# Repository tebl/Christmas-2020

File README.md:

# Christmas 2020
I wanted to do this project last year, but my health deteriorated and so the big Christmas 2019 project became the big Christmas 2020 project instead. 2020, if anything, provided plenty of time for sitting around the house thinking up how to make a blinking LED christmas tree with an Arduino Nano built into it! I even got around to adding a small video of it in action on [YouTube](https://www.youtube.com/watch?v=C256A0oTeUM)!

The project is composed of three PCB designs, parts A/B are the actual tree and have been made so that they slot into eachother. Part C is the base, it holds the Arduino Nano and a couple of shift registers in addition to a switch that is used in order to toggle the various modes (I added a second Part C board to the bottom to add a little more weight).

As with any Christmas tree, you can decorate it with any LEDs though you might need to adjust the resistor values accordingly so that some of them aren't extremely bright (when in doubt, try them on a breadboard first). Alternatively - you could choose to skip the whole decorating step and put some string at the top and hang it from your tree (you will need to use some wire on the bottom to keep it from falling apart).

## Building it
Start by examining all three PCBs, assuming you already have those handy - refer to the BOM below if you're wondering what parts to order from your favourite electronics boutique. Both of the A/B, the two tree parts should have a christmas bauble (at least I think that is the correct English translation of the round glass decorations) specifying both the part name (A or B) and wether you're looking at the front or the back. The latter details, the front and back bit, matters because this is the orientation it needs to be in when you want to slot it into the base (part C).

Because I wanted something that looked good without any components, parts A/B will look different from the standard markings used for LEDs and resistors you would expect to encounter any other time of the year. The baubles with the two holes are for LEDs, you can solder them straight on or aim them upwards if you'd like to - feel free to use those weird LEDs you got as a gift (it's your tree after all) - the important bit is that the **square pad** is for the negative leg of the LED (the **shorter** one). The squiggly lines are for the resistors, you need to pick values that work with your LEDs, so test them in a breadboard first in order to figure out which value to use (or just put 100 Ohm for the dim ones, 330 for the normal LEDs and something like 1K for those bright ones like the blue). Try installing components so that every side gets something, at least that's what my parents always instruct me to do on the big plastic tree.

Parts A/B are attached to the base using right-angle pin headers, take care that you match the orientation to the corresponding parts on part C. While on the subject of part C, the only important part here is that you'll probably need to solder the switch into place before putting in the Arduino Nano (unless you'll be using female header pins so that you can remove it later). The rest of the components (including the Nano) will be installed on the underside of part C.

Given that there are components on the underside of the base, you'll need to add some M3 hex spacers to it so that it won't scrape against the table - if you have an extra part C PCB I recommend putting it on the bottom as well so that it doesn't get knocked around so easily.

## BOM
The BOM, or bill of manufacturing, is a list of the components used when constructing the complete christmas tree. Note that since you can substitute the LEDs/resistors you want to use - the following may be more of a suggestion though you'd need all of it in order to make everything blink. Most of these components should be easily obtainable through your favourite local electronics components store. Right-angle pin headers are usually sold in breakable strips with 40 pins, so just break off 5 pin segments where needed.

| Reference    | Item                                       | Count |
| ------------ | ------------------------------------------ | ----- |
| Christmas A  | Fabricate using Gerber files ([order](https://www.pcbway.com/project/shareproject/Christmas_2020__part_A_.html))   |     1 |
| D1-D9        | LED (3mm or 5mm, colour as wanted)         |     9 |
| R1-R9        | 220, 330 or 1k ohm resistor *              |     9 |
| J1,J2        | 1x5-pin right-angle header                 |     2 |
| Christmas B  | Fabricate using Gerber files ([order](https://www.pcbway.com/project/shareproject/Christmas_2020__part_B_.html))   |     1 |
| D2-D9        | LED (3mm or 5mm, colour as wanted)         |     8 |
| R2-R9        | 220, 330 or 1k ohm resistor *              |     8 |
| J1,J2        | 1x5-pin right-angle header                 |     2 |
| Christmas C  | Fabricate using Gerber files ([order](https://www.pcbway.com/project/shareproject/Christmas_2020__part_C_.html))   |     1 |
| SW1          | SPST momentary push button                 |     1 |
| A1           | Arduino Nano                               |     1 |
| U1,U2        | 74HC595 (DIP-16)                           |     2 |
|              | M3 nylon hex standoffs with screws         |     4 |

*) Use resistors with values that would correspond to the LED you installed, use higher resistrance the brighter the LED (especially the blue ones). If a soldered in LED is too dim, install a lower value on the back as well in order to lower the resistance going to it.

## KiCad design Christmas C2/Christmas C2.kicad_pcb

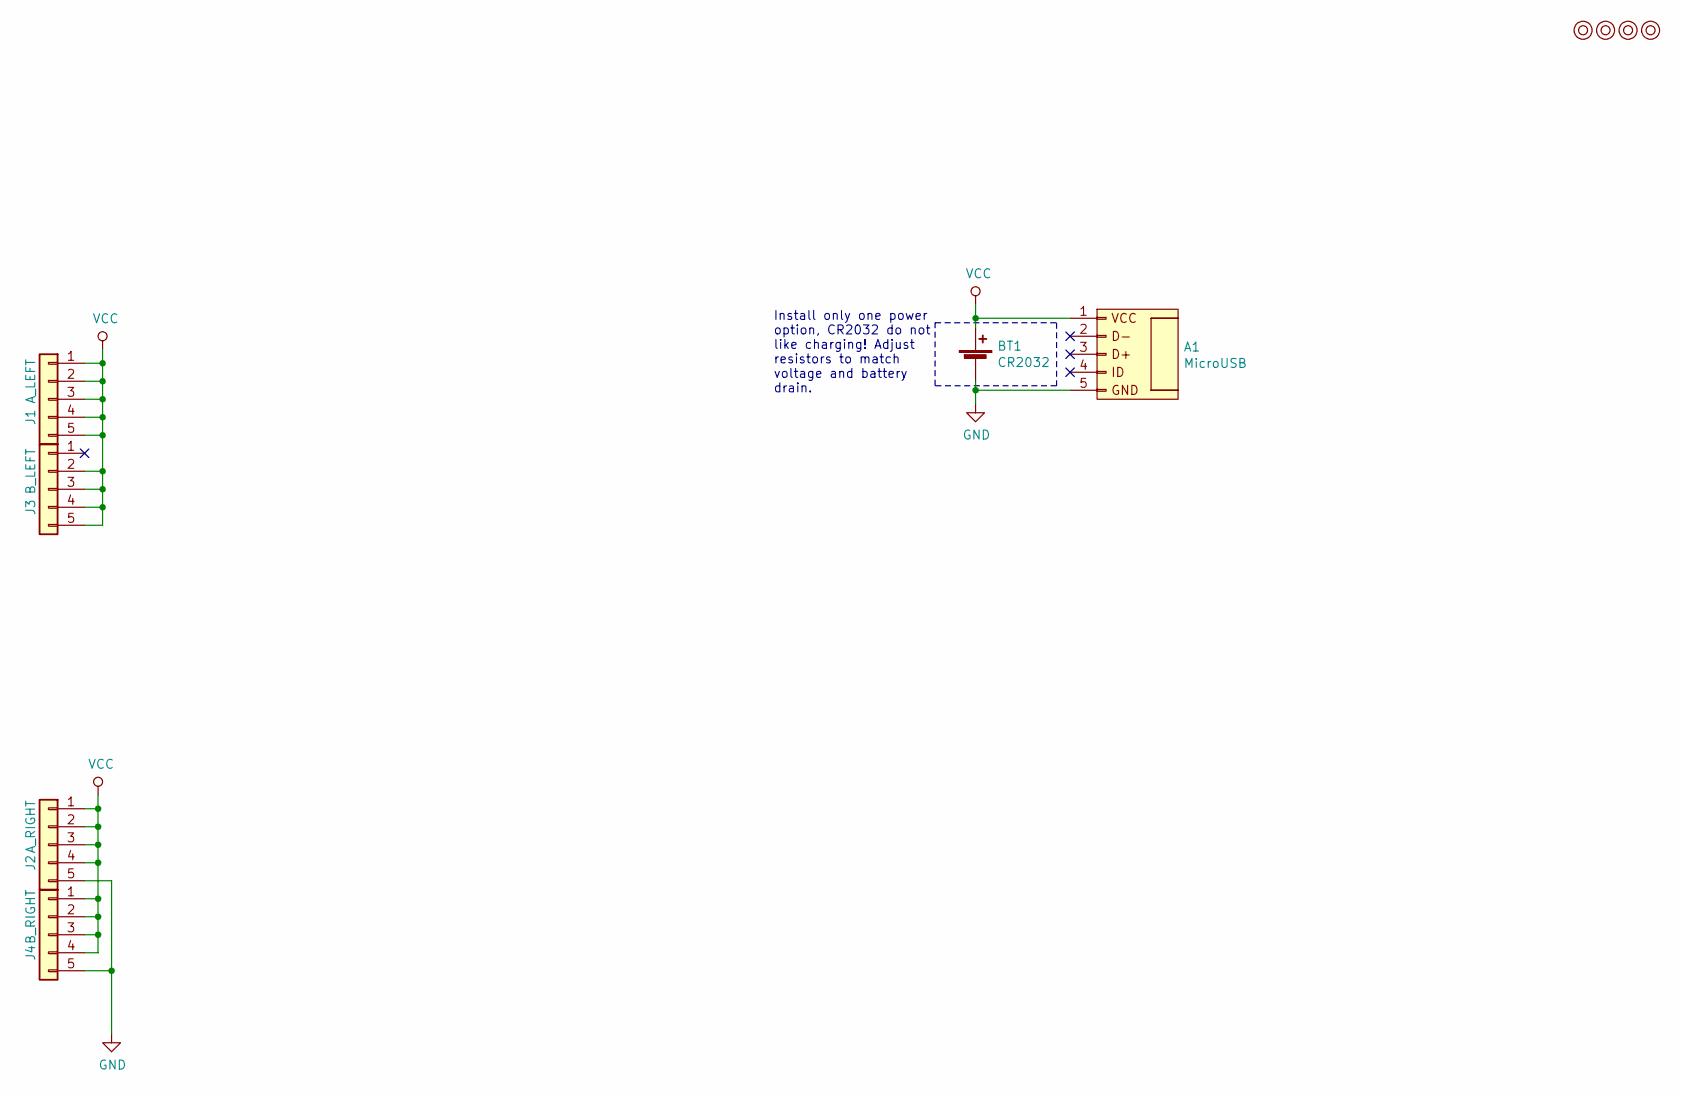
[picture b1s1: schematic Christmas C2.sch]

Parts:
A1: MicroUSB; microusb_breakout
BT1: CR2032; Keystone_103_1x20mm-CoinCell
J1: A_LEFT; conn_base
J2: A_RIGHT; conn_base
J3: B_LEFT; conn_base
J4: B_RIGHT; conn_base
M1, M2, M3, M4: Mounting; M3

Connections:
GND: A1.5 (GND), BT1.2 (-), J2.5, J4.5
VCC: A1.1 (VCC), BT1.1 (+), J1.1, J1.2, J1.3, J1.4, J1.5, J2.1, J2.2, J2.3, J2.4, J3.2, J3.3, J3.4, J3.5, J4.1, J4.2, J4.3, J4.4

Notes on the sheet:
Install only one power option, CR2032 do not like charging! Adjust resistors to match voltage and battery drain.

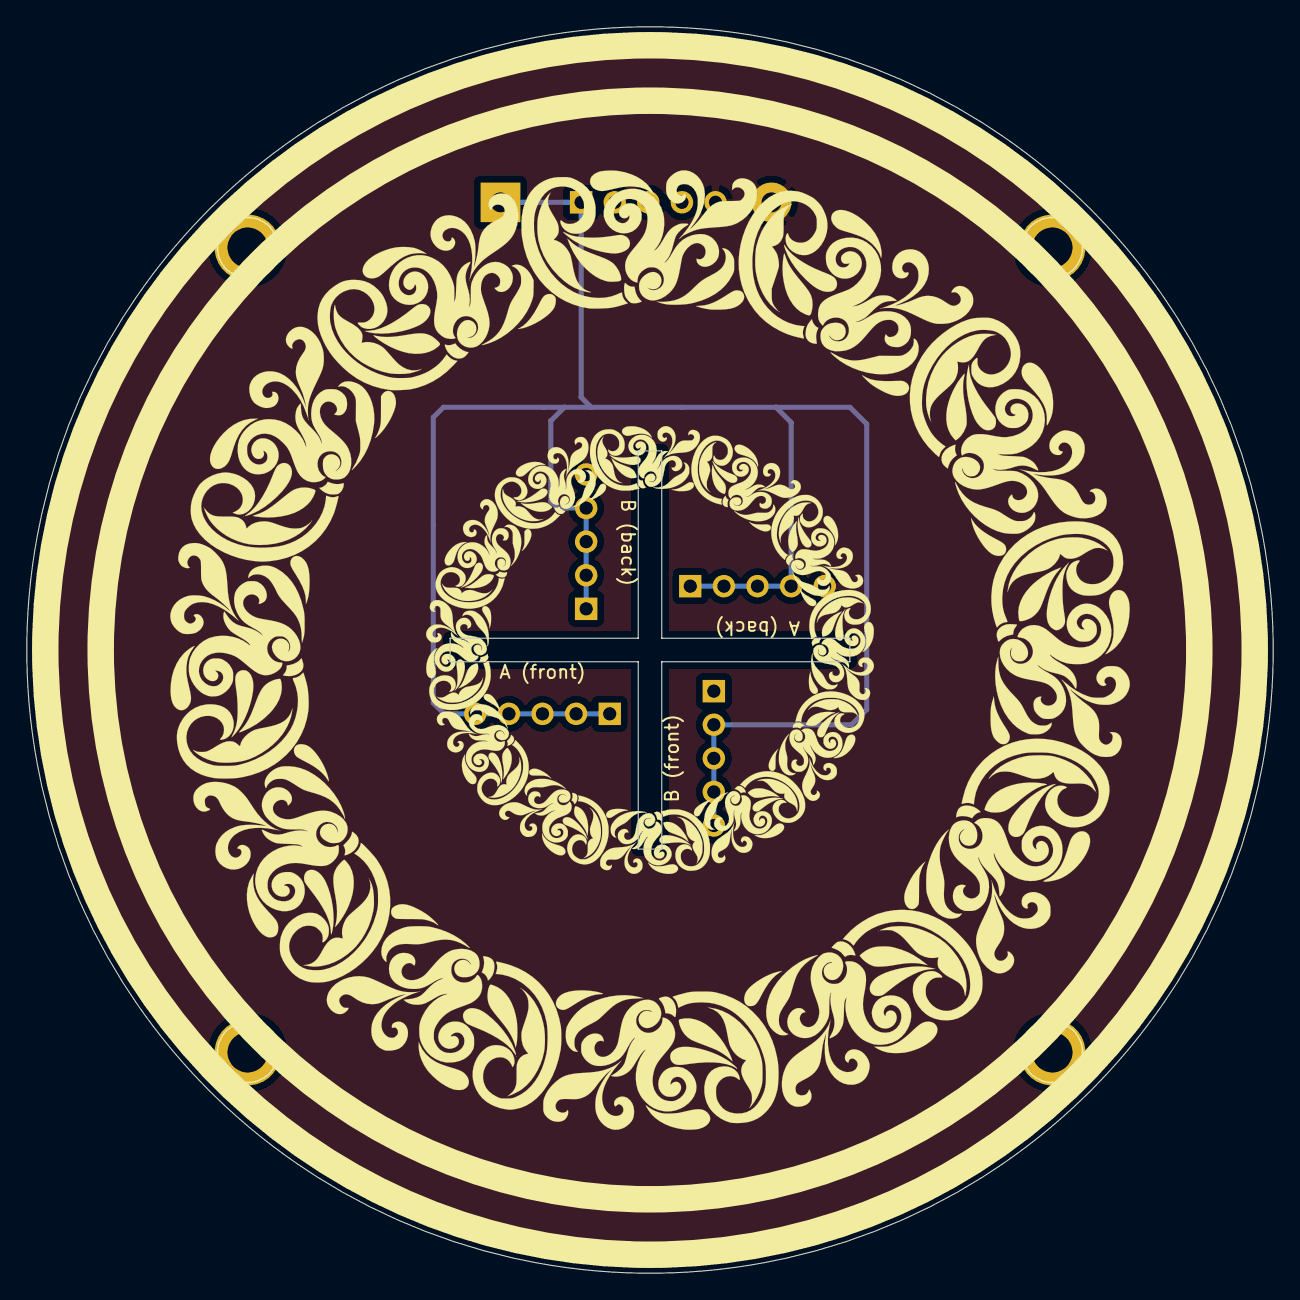
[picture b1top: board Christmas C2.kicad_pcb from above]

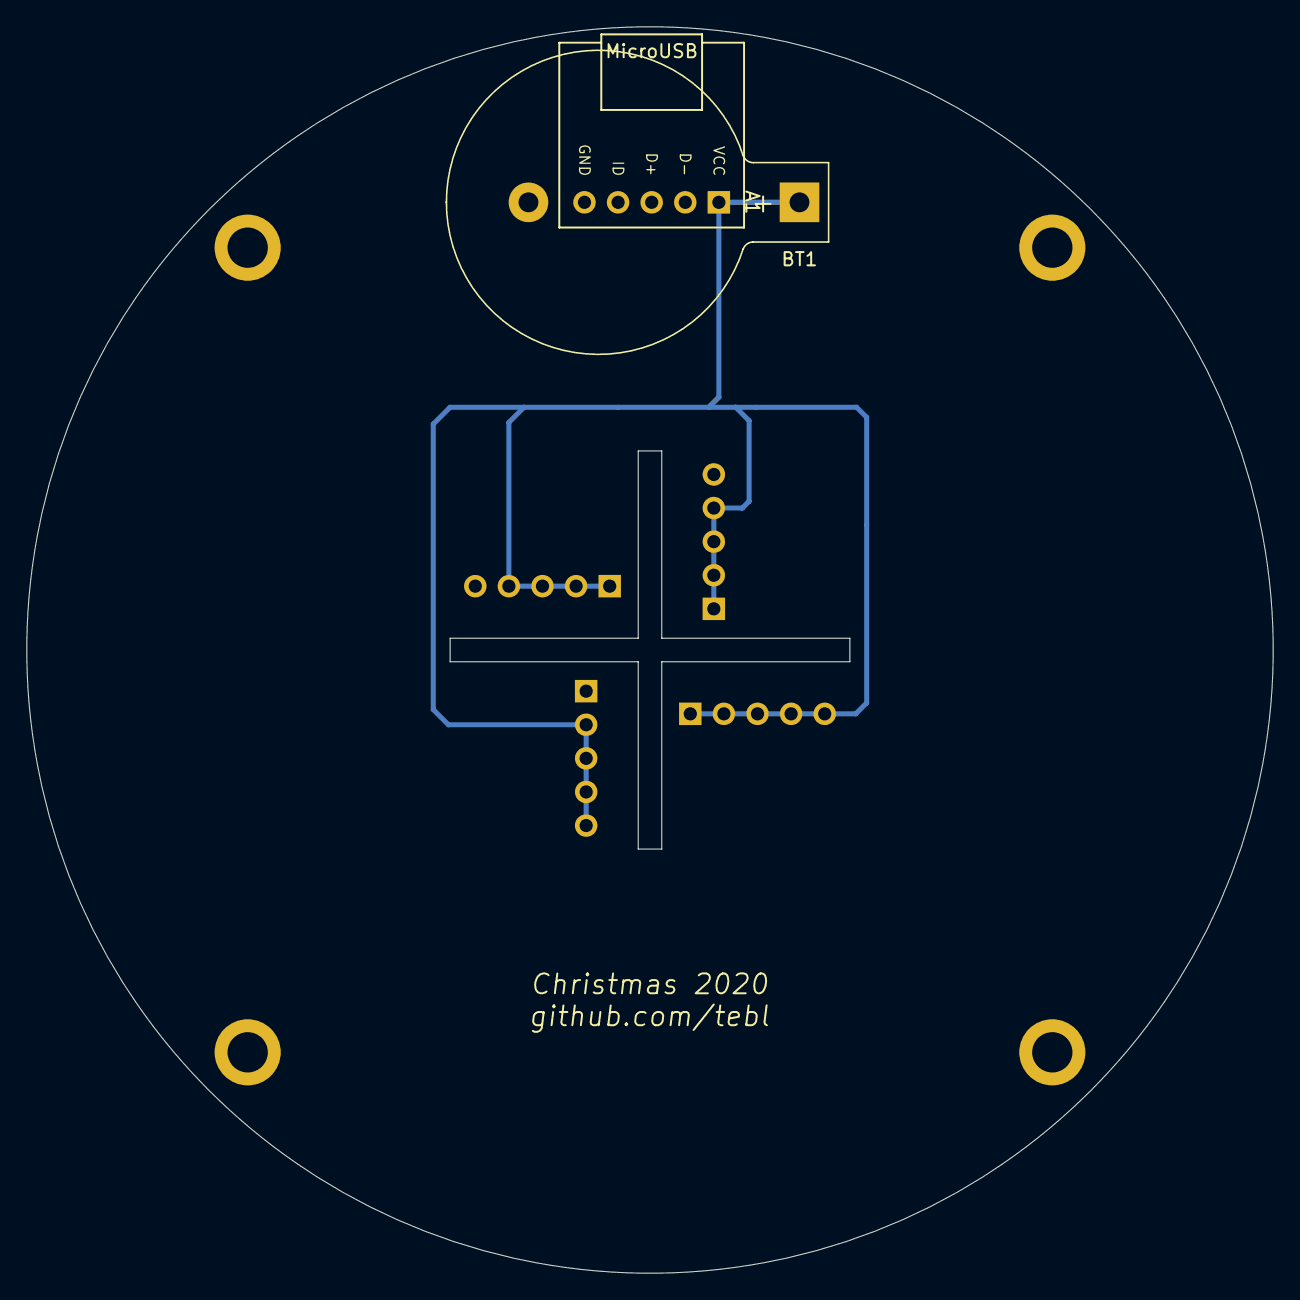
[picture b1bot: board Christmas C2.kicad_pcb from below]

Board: 2 copper layers, 94.2 x 94.2 mm, 10 parts (2 on the bottom side), 2 nets.

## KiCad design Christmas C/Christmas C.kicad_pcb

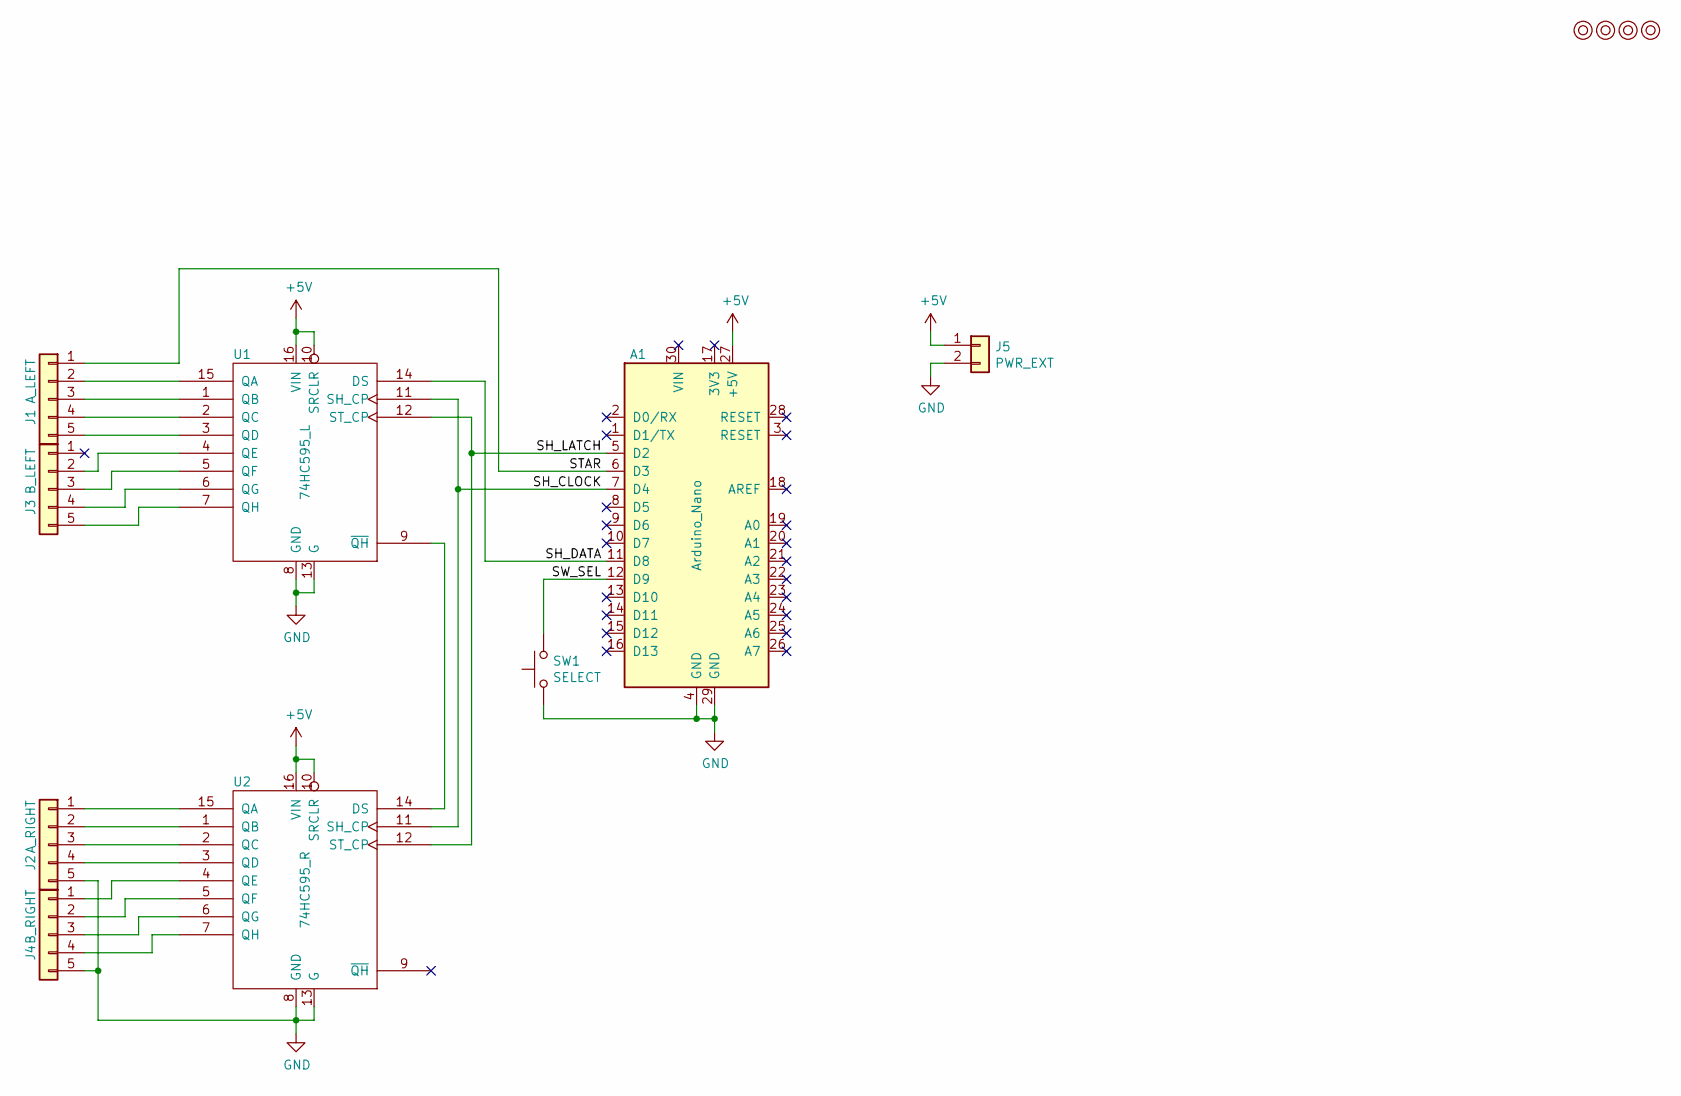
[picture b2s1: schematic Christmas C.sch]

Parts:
A1: Arduino_Nano
J1: A_LEFT; conn_base
J2: A_RIGHT; conn_base
J3: B_LEFT; conn_base
J4: B_RIGHT; conn_base
J5: PWR_EXT; Pin_Header_Straight_1x02_Pitch2.54mm
M1, M2, M3, M4: Mounting; M3
SW1: SELECT; SW_PUSH_6mm
U1: 74HC595_L; DIP-16_W7.62mm_LongPads
U2: 74HC595_R; DIP-16_W7.62mm_LongPads

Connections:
+5V: A1.27 (+5V), J5.1, U1.10 (SRCLR), U1.16 (VIN), U2.10 (SRCLR), U2.16 (VIN)
/SH_CLOCK: A1.7 (D4), U1.11 (SH_CP), U2.11 (SH_CP)
/SH_DATA: A1.11 (D8), U1.14 (DS)
/SH_LATCH: A1.5 (D2), U1.12 (ST_CP), U2.12 (ST_CP)
/STAR: A1.6 (D3), J1.1
/SW_SEL: A1.12 (D9), SW1.2
GND: A1.4 (GND), A1.29 (GND), J2.5, J4.5, J5.2, SW1.1, U1.8 (GND), U1.13 (G), U2.8 (GND), U2.13 (G)
unnamed: J1.2, U1.15 (QA)
unnamed: J1.3, U1.1 (QB)
unnamed: J1.4, U1.2 (QC)
unnamed: J1.5, U1.3 (QD)
unnamed: J2.1, U2.15 (QA)
unnamed: J2.2, U2.1 (QB)
unnamed: J2.3, U2.2 (QC)
unnamed: J2.4, U2.3 (QD)
unnamed: J3.2, U1.4 (QE)
unnamed: J3.3, U1.5 (QF)
unnamed: J3.4, U1.6 (QG)
unnamed: J3.5, U1.7 (QH)
unnamed: J4.1, U2.4 (QE)
unnamed: J4.2, U2.5 (QF)
unnamed: J4.3, U2.6 (QG)
unnamed: J4.4, U2.7 (QH)
unnamed: U1.9 (~QH), U2.14 (DS)

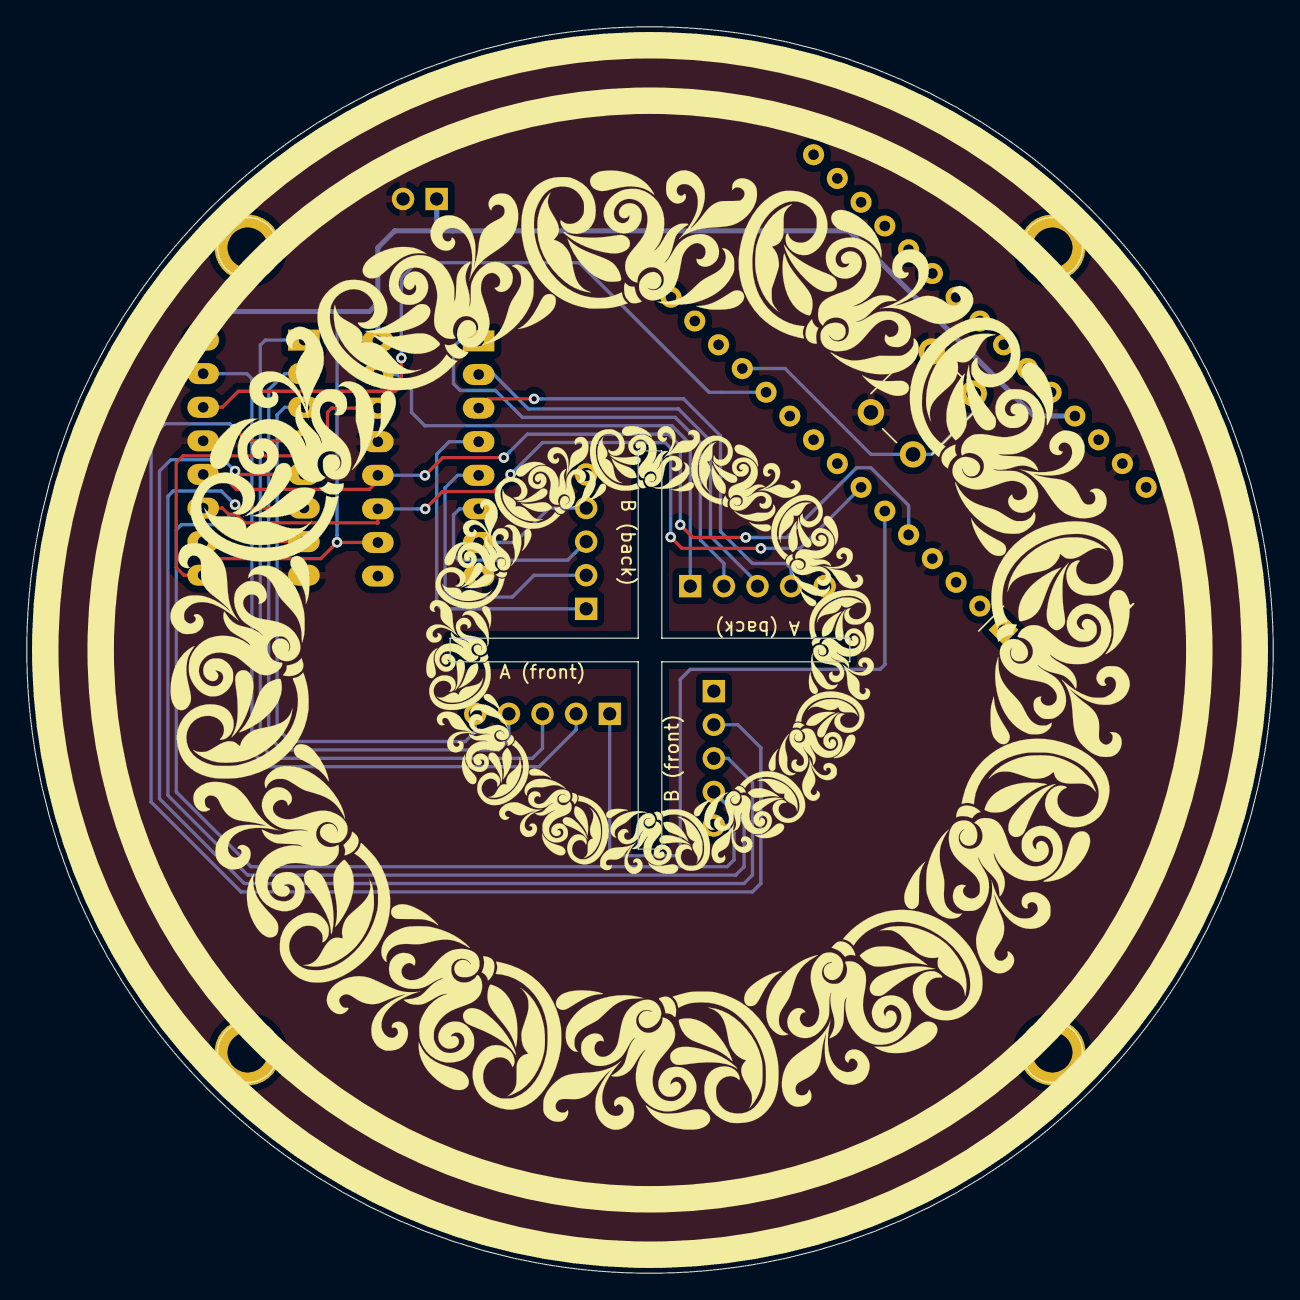
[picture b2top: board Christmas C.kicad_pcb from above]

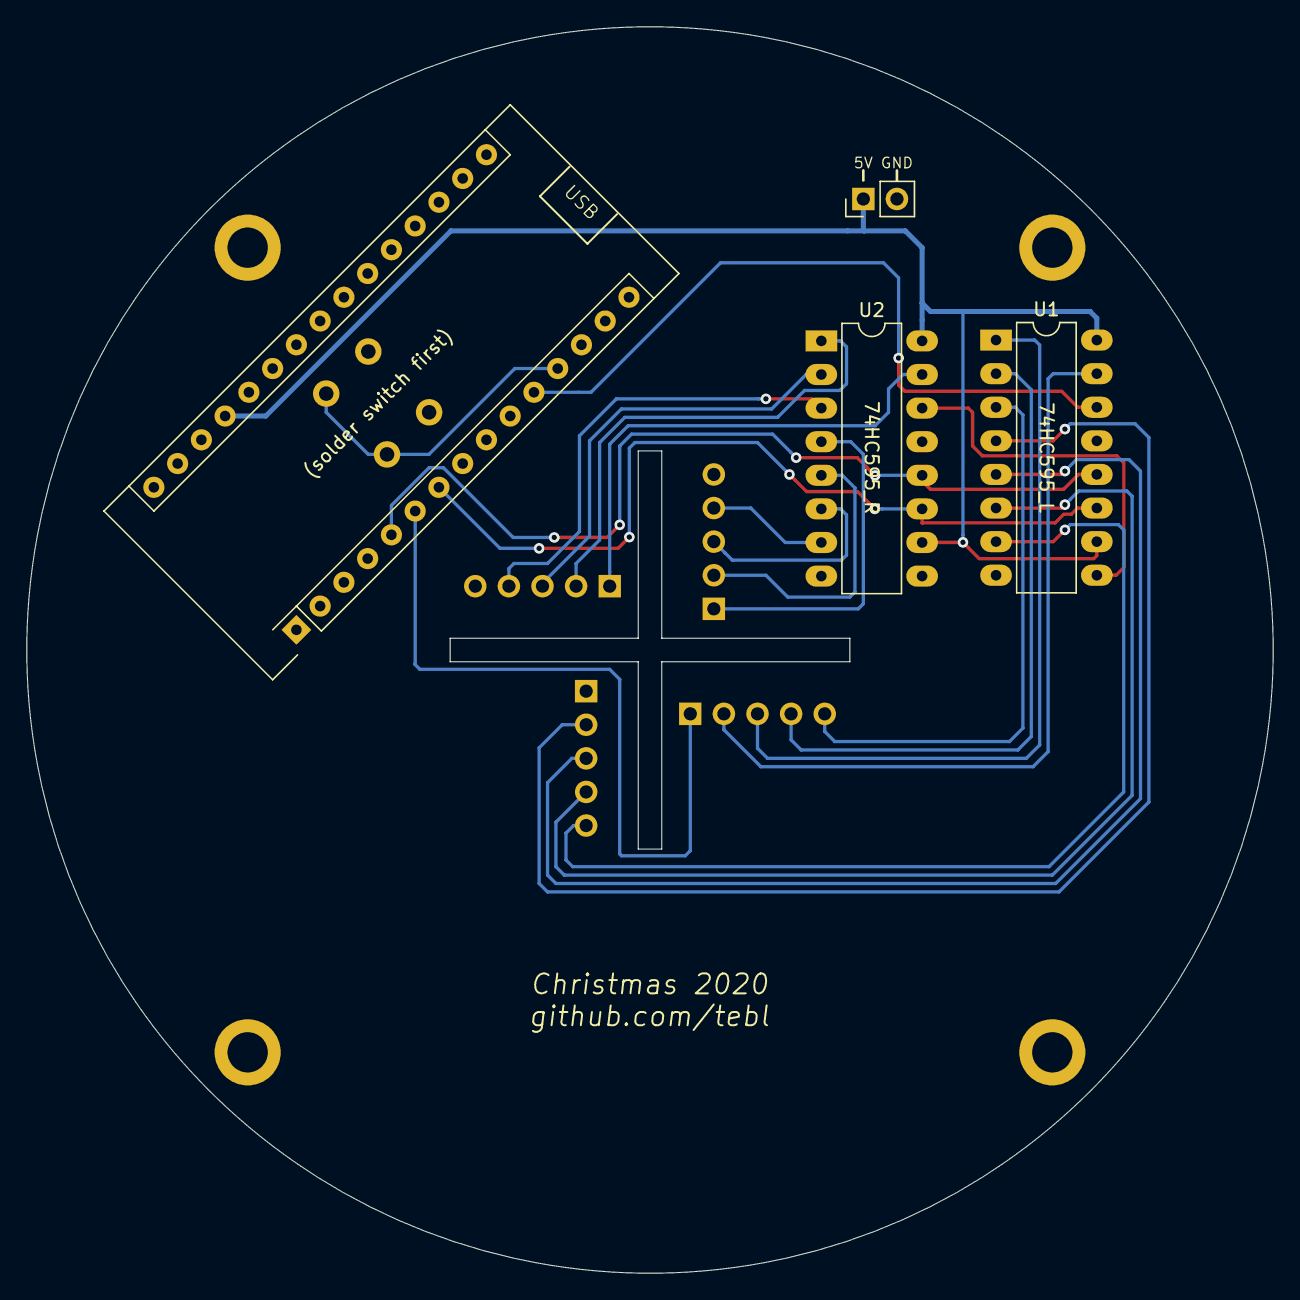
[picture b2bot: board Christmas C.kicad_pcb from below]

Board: 2 copper layers, 94.2 x 94.2 mm, 13 parts (4 on the bottom side), 24 nets.

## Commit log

2020-10-14 Basic tree
2020-10-14 Mirror components
2020-10-14 Stars added
2020-10-15 Changed the top
2020-10-15 Added B side
2020-10-15 Make space at the bottom
2020-10-15 Added base
2020-10-16 Gerber export
2020-10-27 Tweaked bottom connectors
2020-10-28 Changed Nano footprint to something standard
2020-10-28 Added markings to part A
2020-10-28 Added part designation to A/B
2020-10-29 Added arduino sketch
2020-10-31 Updated gerbers
2020-10-31 Gallery added
2020-10-31 README introduction
2020-11-01 Added some code comments
2020-11-01 Added BOM
2020-11-01 Added PCB links for PCBway
2020-11-01 Added image
2020-11-01 Referenced image
2020-11-14 Static version of part C
2020-11-14 Added MicroUSB breakout adapter and battery option to static board
2020-11-14 Add picture
